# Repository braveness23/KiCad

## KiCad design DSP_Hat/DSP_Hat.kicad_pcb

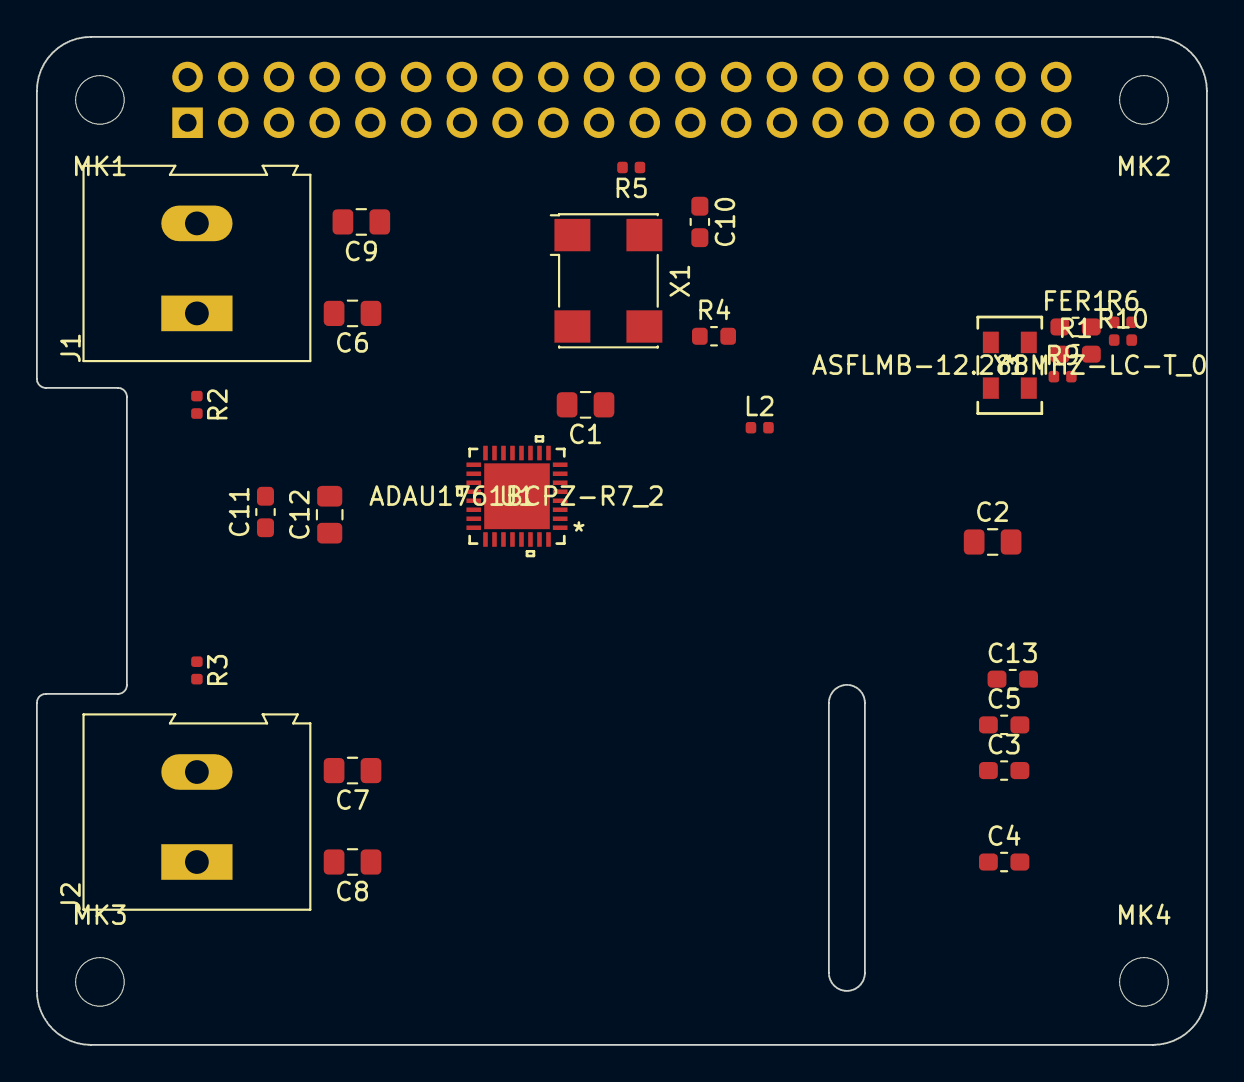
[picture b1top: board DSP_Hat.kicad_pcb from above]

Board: 2 copper layers, 65.0 x 56.0 mm, 33 parts (1 on the bottom side), 16 nets, no tracks yet.

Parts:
C1, C2, C8: 10uF; C_0805_2012Metric_Pad1.15x1.40mm_HandSolder
C3, C5, C10: 10uF; C_0603_1608Metric_Pad1.05x0.95mm_HandSolder
C4: 0.1uF; C_0603_1608Metric_Pad1.05x0.95mm_HandSolder
C6, C7: 0.1uF; C_0805_2012Metric_Pad1.15x1.40mm_HandSolder
C9: 100uF; C_0805_2012Metric_Pad1.15x1.40mm_HandSolder
C11: 100uF; C_0603_1608Metric_Pad1.05x0.95mm_HandSolder
C12: 0.1 uF; C_0805_2012Metric_Pad1.15x1.40mm_HandSolder
C13: 0.1 uF; C_0603_1608Metric_Pad1.05x0.95mm_HandSolder
FER1: 600; L_0603_1608Metric_Pad1.05x0.95mm_HandSolder
J1, J2: AudioJack2_Ground_Switch; TerminalBlock_Altech_AK300-2_P5.00mm
L2: L_Core_Ferrite; L_0402_1005Metric
MK1, MK2, MK3, MK4: M2.5; MountingHole_2.7mm_M2.5
P1: Conn_02x20_Odd_Even; PinSocket_2x20_P2.54mm_Vertical
R1: 10K; R_0603_1608Metric_Pad1.05x0.95mm_HandSolder
R2: 10K; R_0402_1005Metric
R3, R9, R10: 100K; R_0402_1005Metric
R4: 100K; R_0603_1608Metric
R5, R6: 470.0K; R_0402_1005Metric
U1: ADAU1761BCPZ-R7_2; ADAU1761BCPZ-R7
X1: 25MHz; Oscillator_SMD_Abracon_ASV-4Pin_7.0x5.1mm
Y1: ASFLMB-12.288MHZ-LC-T_0; ASFLMB-12.288MHZ-LC-T

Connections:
+3V3: C3.1, C4.1, FER1.2, L2.1, P1.1, P1.17, U1.1, Y1.4
+5V: P1.2, P1.4
GND: C3.2, C4.2, C5.2, C6.2, C7.1, C8.1, C10.2, C12.2, C13.2, P1.6, P1.9, P1.14, P1.20, P1.25, P1.30, P1.34, P1.39, R2.2, R3.1, R4.1, R5.1, R6.1, R9.1, R10.1, U1.9, U1.22, U1.25, U1.33, X1.2, Y1.2
unnamed: C1.1, R6.2, U1.11
unnamed: C1.2, R4.2
unnamed: C2.1, R5.2, U1.13
unnamed: C2.2, R3.2
unnamed: C5.1, C6.1, U1.24
unnamed: C7.2, C8.2, U1.4, U1.6, U1.7, U1.10, U1.12, U1.14
unnamed: C9.1, U1.20
unnamed: C9.2, R9.2
unnamed: C10.1, C12.1, C13.1, FER1.1, U1.8, U1.23
unnamed: L2.2, X1.4
unnamed: C11.1, U1.19
unnamed: C11.2, R10.2
unnamed: R1.2, R2.1, Y1.1

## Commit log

2019-04-02 more work on timing crytal
2019-04-02 more work on schematic
2019-04-03 farted around some more with DSP Hat
2019-04-05 placing more PCB footprints
2019-04-07 overhaul of schematic
2019-04-08 edits to symbol for ADAU1761
2019-04-08 what are your values?
2019-04-10 added osc
2019-04-14 annotate parts
2019-04-15 associating footprints to symbols
2019-04-16 futher matching of footprints to symbols
2019-04-16 corrected path for missing library
2019-04-19 I hate working with KiCad symbol and footprint libraries

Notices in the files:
parts and their libraries:
Copyright 2016 Accelerated Designs. All rights reserved.
